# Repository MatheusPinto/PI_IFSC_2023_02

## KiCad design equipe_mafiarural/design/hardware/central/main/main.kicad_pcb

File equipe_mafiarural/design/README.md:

<!-- PROJECT LOGO -->
<div align="center">
  <h3 align="center">Sistema de Monitoramento de Vazamento de Gás de Cozinha</h3>

  <p align="center">
    <strong>(Design)</strong>
    <br />
</div>

## Índice

<!-- TABLE OF CONTENTS -->
<details>
  <summary>Table of Contents</summary>
  <ol>
    <li>
      <a href="#introdução">Introdução</a>
    </li>
    <li>
      <a href="#esquemático-de-funcionamento">Esquemático de Funcionamento</a>
      <ul>
        <li><a href="#módulo-central">Módulo Central</a></li>
        <li><a href="#módulo-de-sensoriamento">Módulo de Sensoriamento</a></li>
      </ul>
    </li>
    <li>
      <a href="#layout-da-placa-de-circuito-impresso">Layout da Placa de Circuito Impresso</a>
      <ul>
        <li><a href="#módulo-central-1">Módulo Central</a></li>
        <li><a href="#módulo-de-sensoriamento-1">Módulo de Sensoriamento</a></li>
      </ul>
    </li>
    <li>
      <a href="#modelo-3d-do-sistema">Modelo 3D do Sistema</a>
    </li>
    <li>
      <a href="#software">Software</a>
    </li>
  </ol>
</details>

---

## Introdução

Este documento detalha o design do projeto de um sistema de monitoramento de vazamento de gás de cozinha. O sistema será composto por um módulo central e dois módulos de sensoriamento.

## Esquemático de Funcionamento

O esquemático abaixo ilustra como funcionará a lógica do sistema. No caso deste projeto, serão utilizados apenas dois sensores que estarão conectados à central via rede, que por sua vez transmitirá os logs de monitoramento para o servidor ThingSpeak. 

<div style="display: flex; width: 100%; align-items: center; justify-content: space-around; gap: 20px;">

</div>
<br />

### Módulo Central

<br />

### Módulo de Sensoriamento

<br />

## Layout da Placa de Circuito Impresso

### Módulo Central

O módulo central terá entrada de 5 -12V e estará posicionada dentro do quadro de distribuição da residência. Para fazer o controle será utilizado um módulo de relés. Para o mantimento da alimentação após o corte de energia haverá uma célula Li-ion de 3.7V, sendo possível a expansão em paralelo para aumentar a capacidade de armazenamento.

<br />

### Módulo de Sensoriamento

O módulo de sensoriamento terá entrada de 5V via microUSB. Para o mantimento da alimentação após o corte de energia haverá uma célula Li-ion de 3.7V, sendo possível a expansão em paralelo para aumentar a capacidade de armazenamento.

<br />

## Modelo 3D do Sistema

Os sensores tem a principal qualidade de possibilitar a opção de o próprio usuário alocar sua posição. O recomendado é o mais próximo possível do chão e da potencial fonte de vazamento, considerando a densidade dos gases que desejamos detectar. No modelo abaixo, há dois sensores: Um posicionado logo ao lado da geladeira e outro acima da pia. A case ilustrada no modelo é apenas ilustrativa, não sendo a versão final do produto. A versão final da case estará disponível após testes com a placa e decisão final de componentes e periféricos.

<br />

## Software

A parte de monitoramento de logs e emissão de notificação será feita pelo servidor ThingSpeak. O código para o ESP32 será desenvolvido em C/C++ na IDE do Arduino. Como EXTRA, há a possibilidade de armazenar os comandos de controle em um cartão SD no módulo central, para que seja possível a atuação do sistema em caso de falha de conexão com a internet.

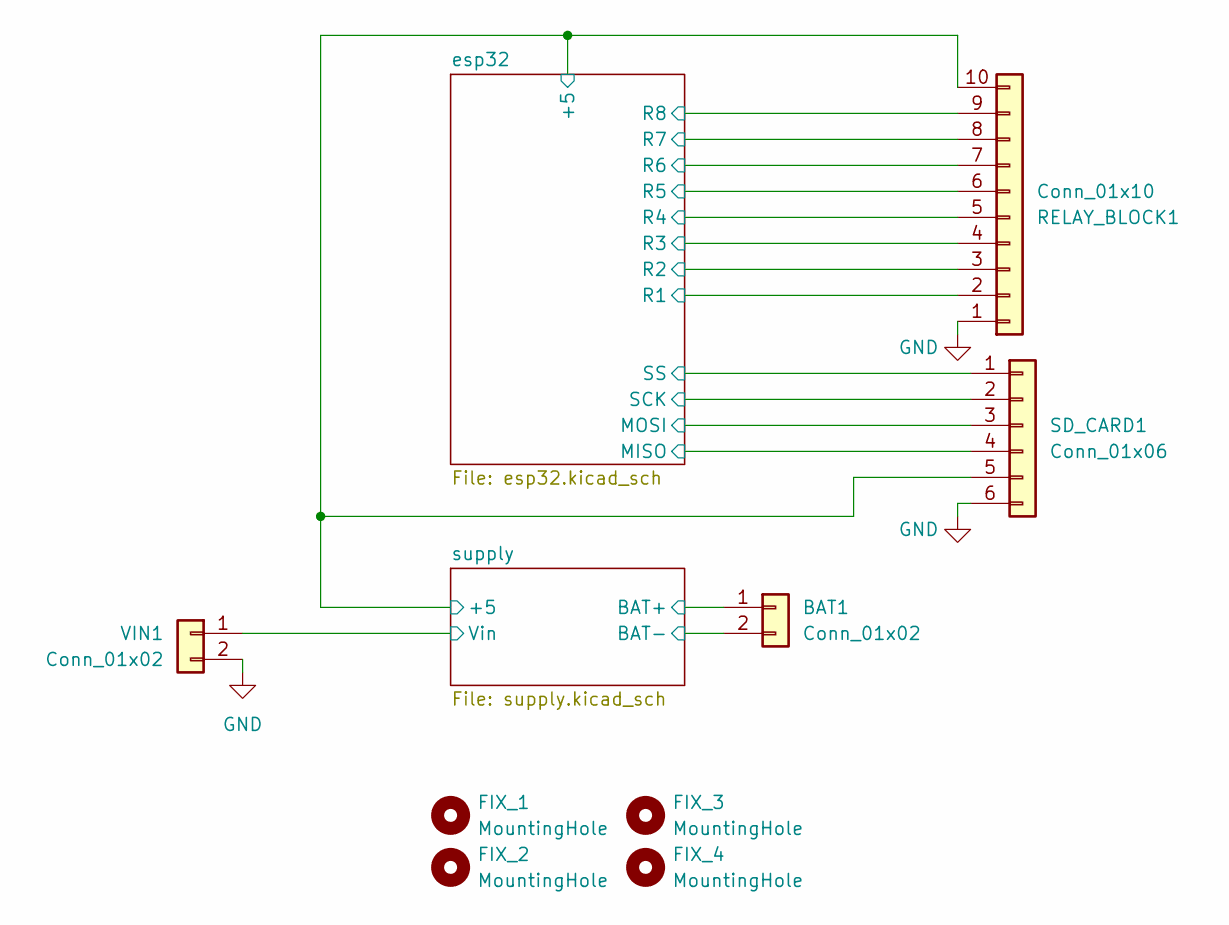
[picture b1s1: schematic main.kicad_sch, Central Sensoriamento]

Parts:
BAT1: Conn_01x02; PinHeader_1x02_P2.54mm_Vertical
FIX_1, FIX_2, FIX_3, FIX_4: MountingHole; MountingHole_3.5mm_Pad
RELAY_BLOCK1: Conn_01x10; PinSocket_1x10_P2.54mm_Vertical
SD_CARD1: Conn_01x06; PinSocket_1x06_P2.54mm_Vertical
VIN1: Conn_01x02; TerminalBlock_bornier-2_P5.08mm

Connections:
/esp32/+5: RELAY_BLOCK1.10, SD_CARD1.5; also elsewhere on the board
/esp32/MISO: SD_CARD1.4; also elsewhere on the board
/esp32/MOSI: SD_CARD1.3; also elsewhere on the board
/esp32/R1: RELAY_BLOCK1.2; also elsewhere on the board
/esp32/R2: RELAY_BLOCK1.3; also elsewhere on the board
/esp32/R3: RELAY_BLOCK1.4; also elsewhere on the board
/esp32/R4: RELAY_BLOCK1.5; also elsewhere on the board
/esp32/R5: RELAY_BLOCK1.6; also elsewhere on the board
/esp32/R6: RELAY_BLOCK1.7; also elsewhere on the board
/esp32/R7: RELAY_BLOCK1.8; also elsewhere on the board
/esp32/R8: RELAY_BLOCK1.9; also elsewhere on the board
/esp32/SCK: SD_CARD1.2; also elsewhere on the board
/esp32/SS: SD_CARD1.1; also elsewhere on the board
/supply/BAT+: BAT1.1; also elsewhere on the board
/supply/Vin: VIN1.1; also elsewhere on the board
GND: BAT1.2, RELAY_BLOCK1.1, SD_CARD1.6, VIN1.2; also elsewhere on the board

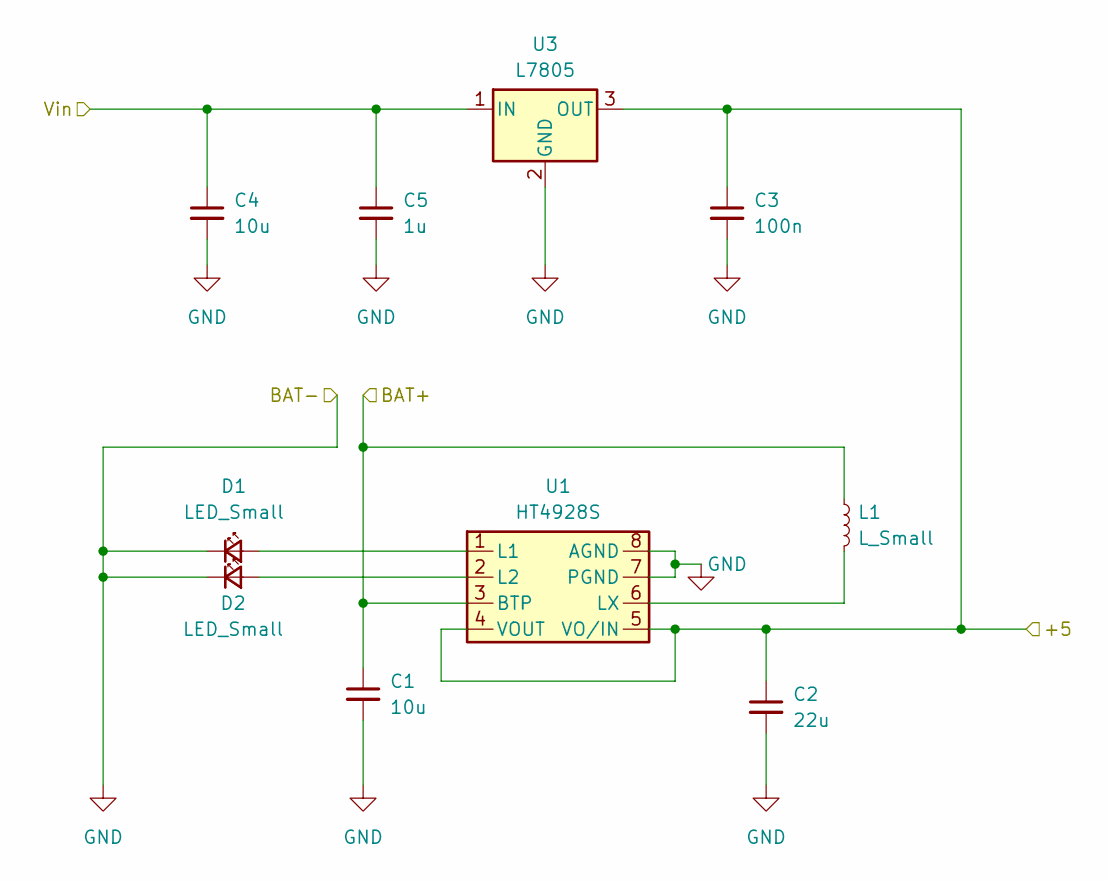
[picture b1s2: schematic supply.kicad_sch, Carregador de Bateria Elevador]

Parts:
C1: 10u; C_0805_2012Metric_Pad1.18x1.45mm_HandSolder
C2: 22u; C_1210_3225Metric_Pad1.33x2.70mm_HandSolder
C3: 100n; C_0805_2012Metric_Pad1.18x1.45mm_HandSolder
C4: 10u; CP_Radial_D5.0mm_P2.50mm
C5: 1u; CP_Radial_D5.0mm_P2.50mm
D1, D2: LED_Small; D_0805_2012Metric_Pad1.15x1.40mm_HandSolder
L1: L_Small; L_1812_4532Metric_Pad1.30x3.40mm_HandSolder
U1: HT4928S; SOP-8_3.9x4.9mm_P1.27mm
U3: L7805; TO-220-3_Vertical

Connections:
/esp32/+5: C2.1, C3.1, U1.4 (VOUT), U1.5 (VO/IN), U3.3 (OUT); also elsewhere on the board
/supply/BAT+: C1.1, L1.1, U1.3 (BTP); also elsewhere on the board
/supply/Vin: C4.1, C5.1, U3.1 (IN); also elsewhere on the board
GND: C1.2, C2.2, C3.2, C4.2, C5.2, D1.1 (K), D2.1 (K), U1.7 (PGND), U1.8 (AGND), U3.2 (GND); also elsewhere on the board
unnamed: D1.2 (A), U1.1 (L1)
unnamed: D2.2 (A), U1.2 (L2)
unnamed: L1.2, U1.6 (LX)

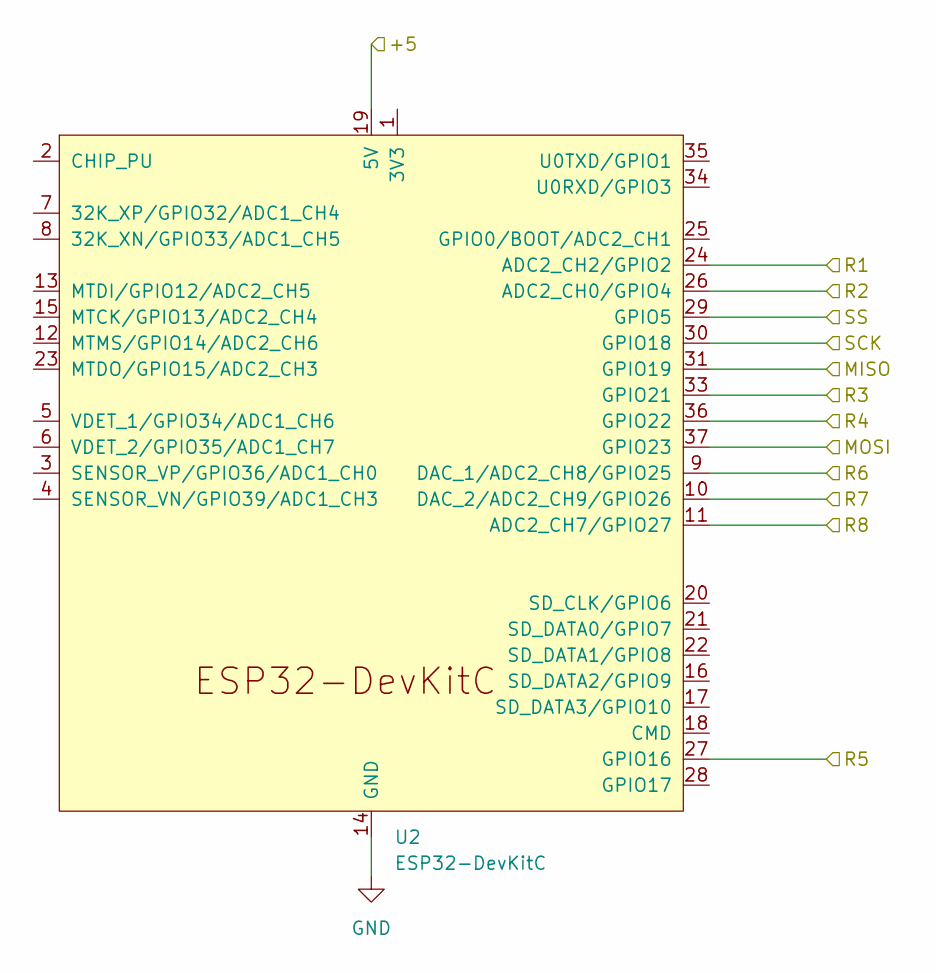
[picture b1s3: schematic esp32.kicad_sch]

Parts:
U2: ESP32-DevKitC

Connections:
/esp32/+5: U2.19 (5V); also elsewhere on the board
/esp32/MISO: U2.31 (GPIO19); also elsewhere on the board
/esp32/MOSI: U2.37 (GPIO23); also elsewhere on the board
/esp32/R1: U2.24 (ADC2_CH2/GPIO2); also elsewhere on the board
/esp32/R2: U2.26 (ADC2_CH0/GPIO4); also elsewhere on the board
/esp32/R3: U2.33 (GPIO21); also elsewhere on the board
/esp32/R4: U2.36 (GPIO22); also elsewhere on the board
/esp32/R5: U2.27 (GPIO16); also elsewhere on the board
/esp32/R6: U2.9 (DAC_1/ADC2_CH8/GPIO25); also elsewhere on the board
/esp32/R7: U2.10 (DAC_2/ADC2_CH9/GPIO26); also elsewhere on the board
/esp32/R8: U2.11 (ADC2_CH7/GPIO27); also elsewhere on the board
/esp32/SCK: U2.30 (GPIO18); also elsewhere on the board
/esp32/SS: U2.29 (GPIO5); also elsewhere on the board
GND: U2.14 (GND), U2.32 (GND), U2.38 (GND); also elsewhere on the board

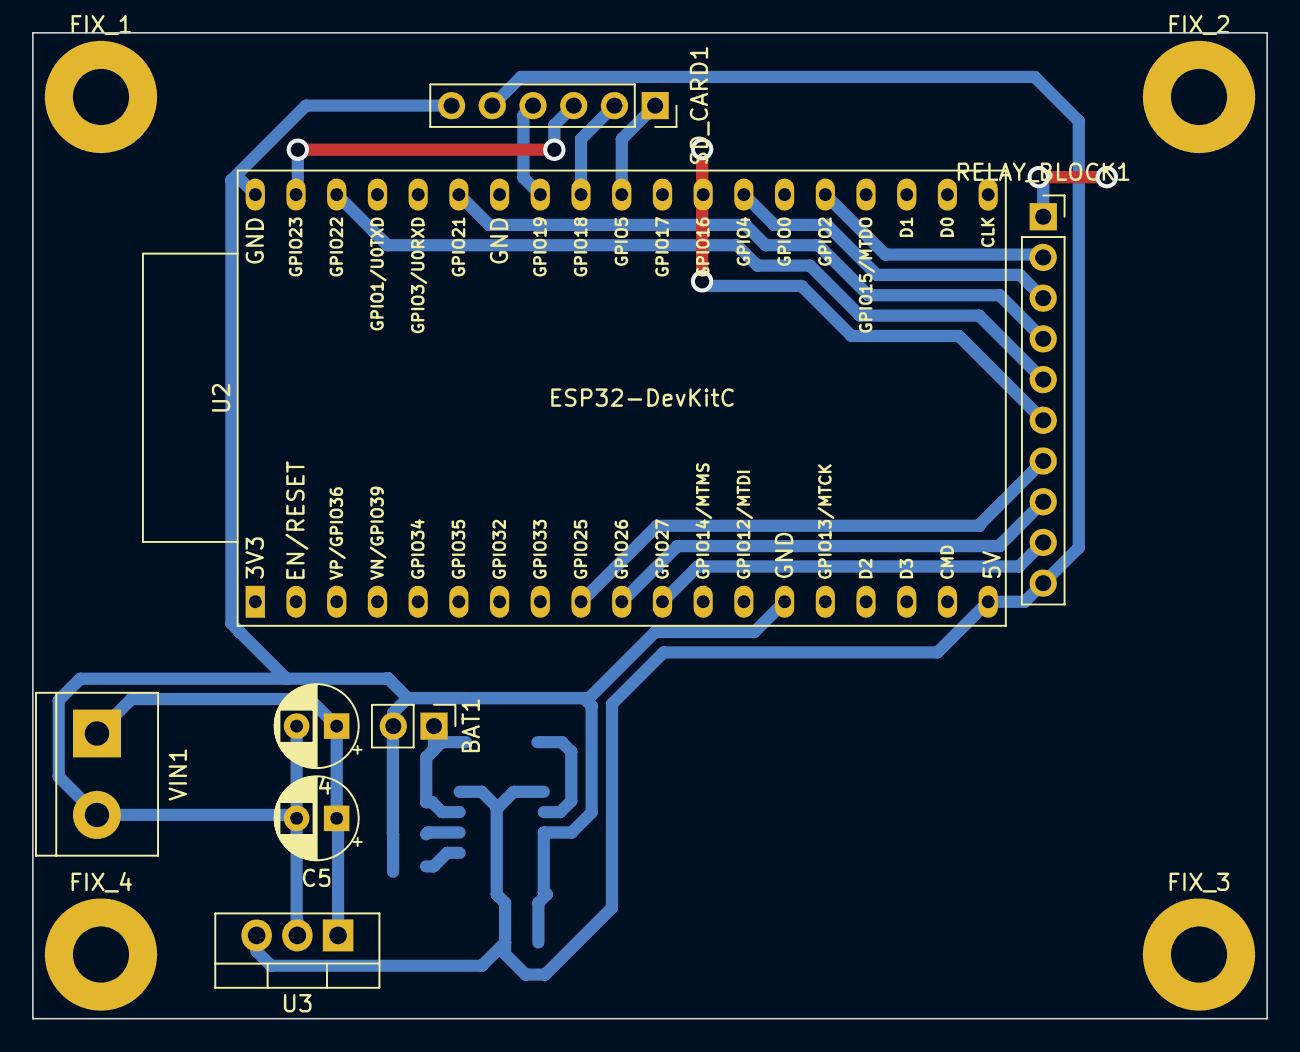
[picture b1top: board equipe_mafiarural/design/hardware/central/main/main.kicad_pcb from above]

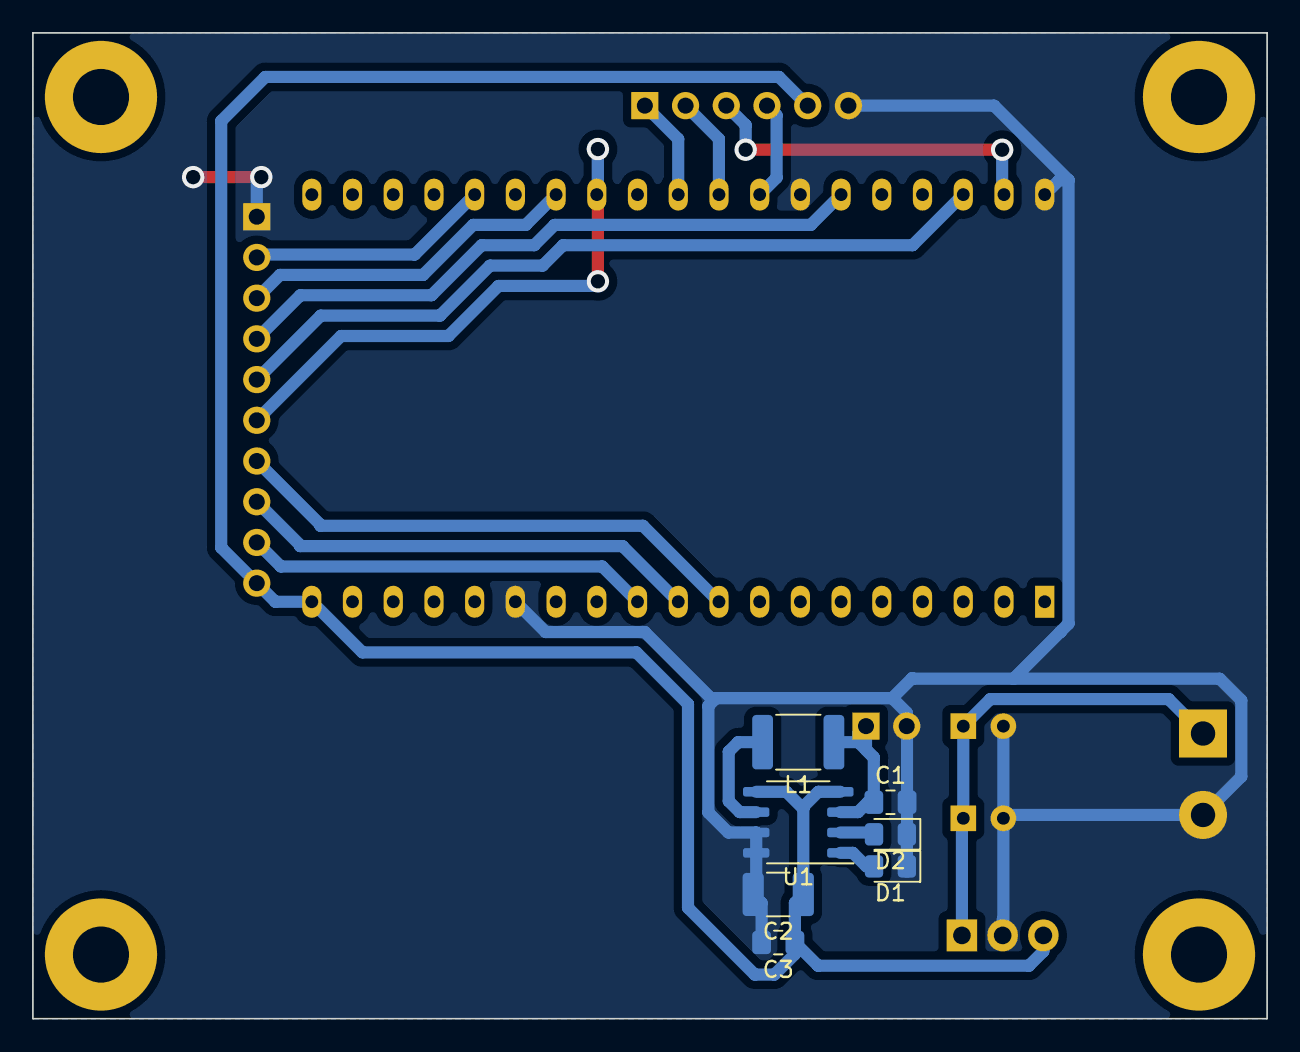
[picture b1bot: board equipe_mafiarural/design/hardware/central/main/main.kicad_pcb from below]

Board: 2 copper layers, 77.0 x 61.5 mm, 19 parts (7 on the bottom side), 19 nets.

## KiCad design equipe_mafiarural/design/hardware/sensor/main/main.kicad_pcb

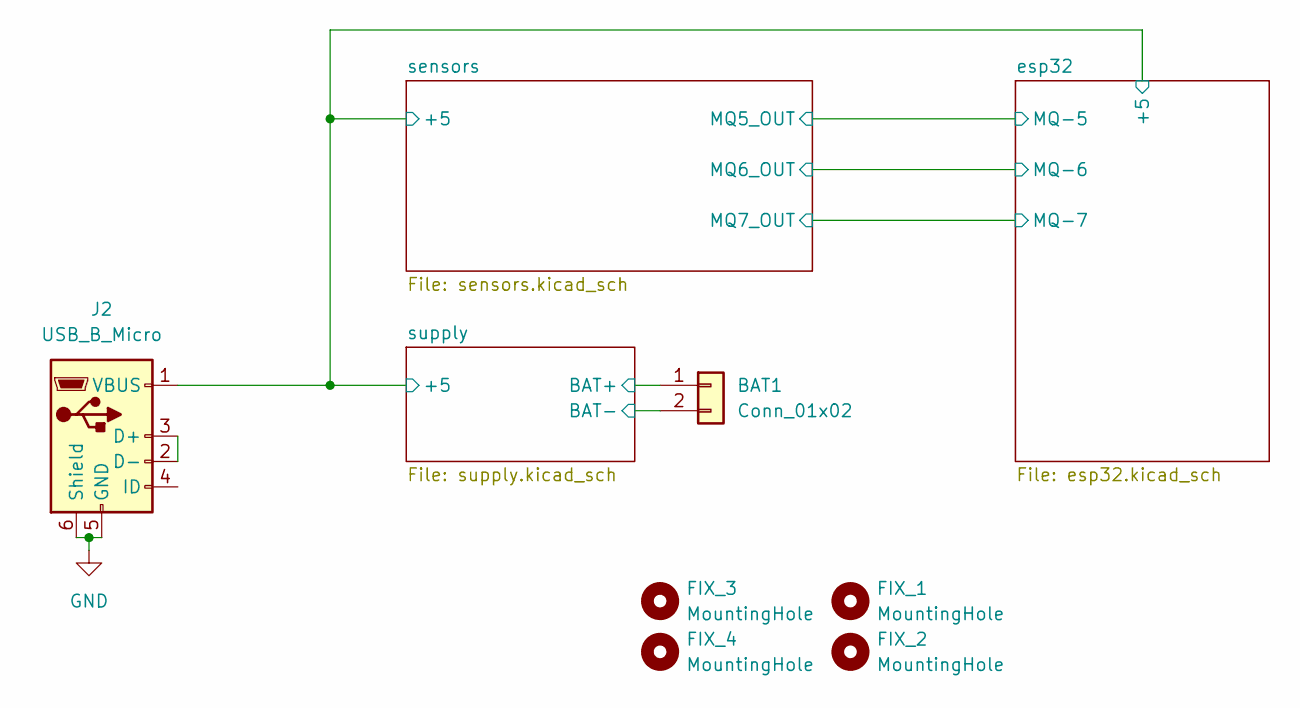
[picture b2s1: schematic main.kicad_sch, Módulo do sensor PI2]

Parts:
BAT1: Conn_01x02; PinHeader_1x02_P2.54mm_Vertical
FIX_1, FIX_2, FIX_3, FIX_4: MountingHole; MountingHole_3.5mm_Pad
J2: USB_B_Micro; USB_Micro-B_Amphenol_10118193-0002LF_Horizontal

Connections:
/esp32/+5: J2.1 (VBUS); also elsewhere on the board
/supply/BAT+: BAT1.1; also elsewhere on the board
GND: BAT1.2, J2.5 (GND), J2.6 (Shield); also elsewhere on the board

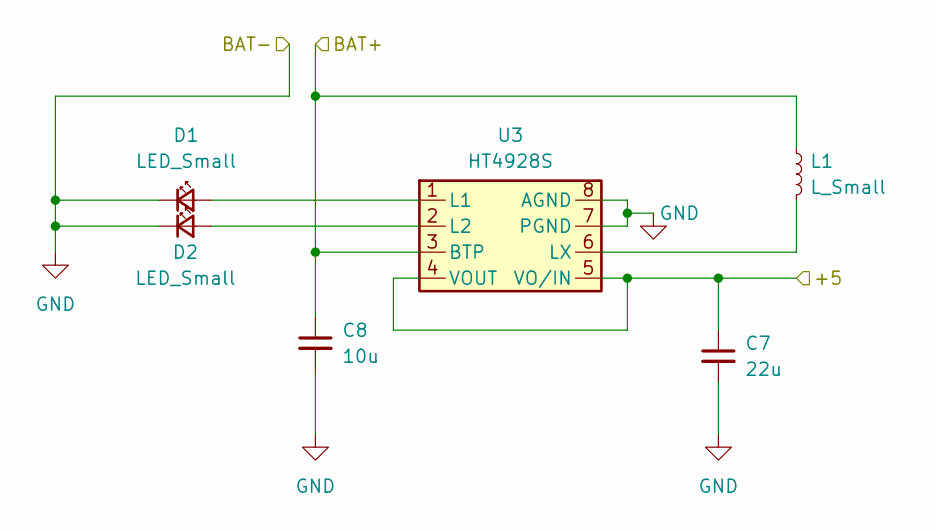
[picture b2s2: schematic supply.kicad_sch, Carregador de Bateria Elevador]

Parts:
C7: 22u; C_1210_3225Metric_Pad1.33x2.70mm_HandSolder
C8: 10u; C_0805_2012Metric_Pad1.18x1.45mm_HandSolder
D1, D2: LED_Small; D_0805_2012Metric_Pad1.15x1.40mm_HandSolder
L1: L_Small; L_1812_4532Metric_Pad1.30x3.40mm_HandSolder
U3: HT4928S; SOP-8_3.9x4.9mm_P1.27mm

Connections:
/esp32/+5: C7.1, U3.4 (VOUT), U3.5 (VO/IN); also elsewhere on the board
/supply/BAT+: C8.1, L1.1, U3.3 (BTP); also elsewhere on the board
GND: C7.2, C8.2, D1.1 (K), D2.1 (K), U3.7 (PGND), U3.8 (AGND); also elsewhere on the board
unnamed: D1.2 (A), U3.1 (L1)
unnamed: D2.2 (A), U3.2 (L2)
unnamed: L1.2, U3.6 (LX)

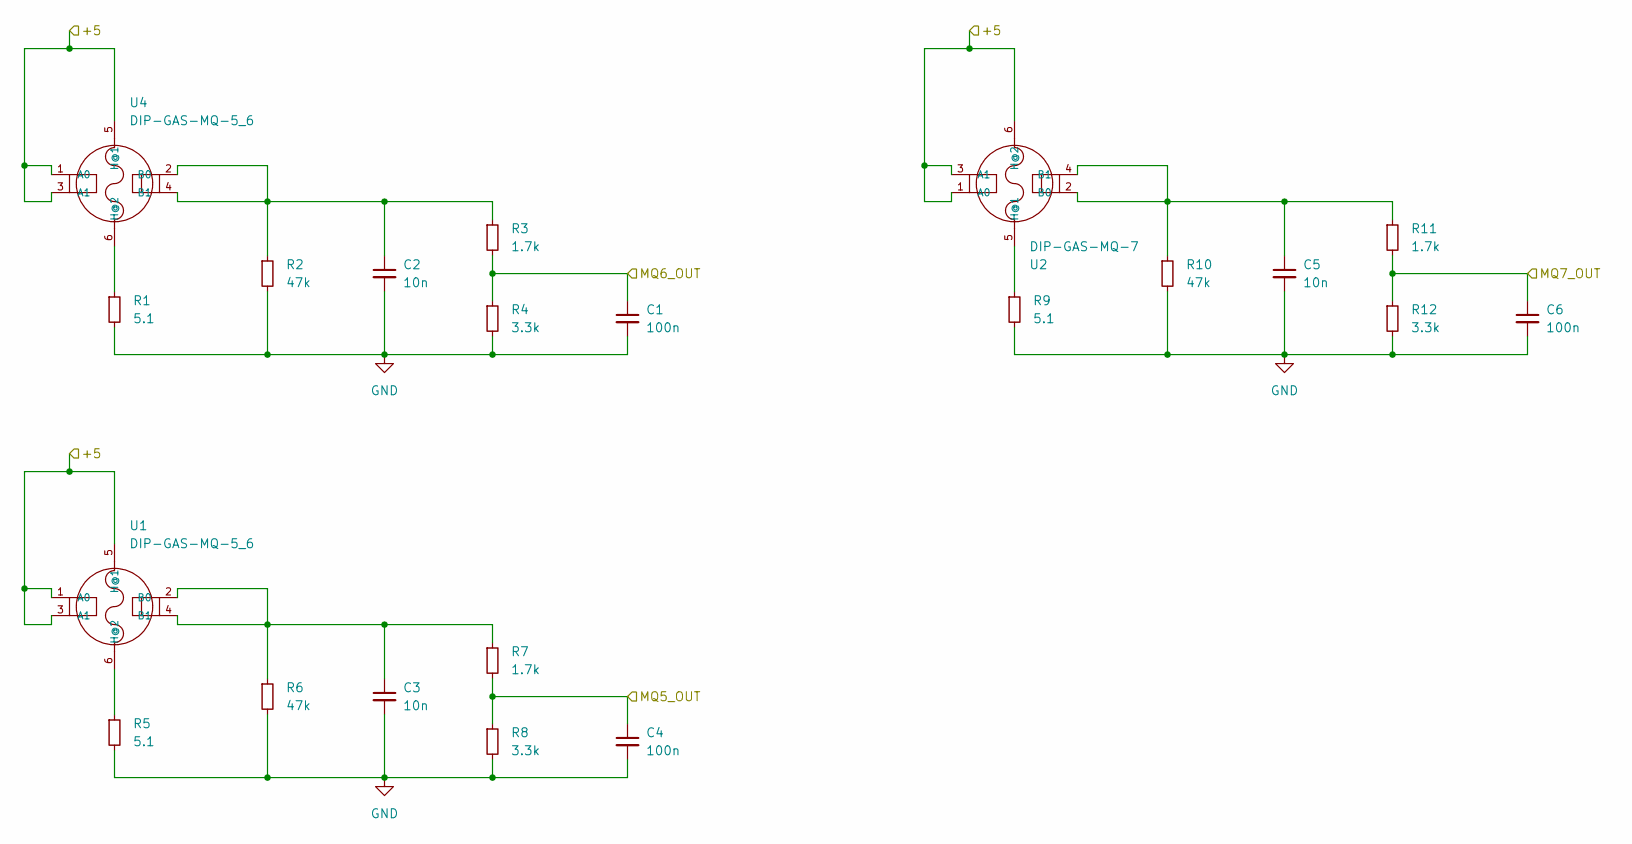
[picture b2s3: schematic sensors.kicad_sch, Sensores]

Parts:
C1, C4, C6: 100n; C_0805_2012Metric_Pad1.18x1.45mm_HandSolder
C2, C3, C5: 10n; C_0805_2012Metric_Pad1.18x1.45mm_HandSolder
R1, R5, R9: 5.1; R_0805_2012Metric_Pad1.20x1.40mm_HandSolder
R2, R6, R10: 47k; R_0805_2012Metric_Pad1.20x1.40mm_HandSolder
R3, R7, R11: 1.7k; R_0805_2012Metric_Pad1.20x1.40mm_HandSolder
R4, R8, R12: 3.3k; R_0805_2012Metric_Pad1.20x1.40mm_HandSolder
U1, U4: DIP-GAS-MQ-5_6; SNR6; MPN MQ-5
U2: DIP-GAS-MQ-7; MQ-7; MPN MQ-5

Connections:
/esp32/+5: U1.1 (A0), U1.3 (A1), U1.5 (H@1), U2.1 (A0), U2.3 (A1), U2.6 (H@2), U4.1 (A0), U4.3 (A1), U4.5 (H@1); also elsewhere on the board
/esp32/MQ-5: C4.1, R7.2, R8.1; also elsewhere on the board
/esp32/MQ-6: C1.1, R3.2, R4.1; also elsewhere on the board
/esp32/MQ-7: C6.1, R11.2, R12.1; also elsewhere on the board
GND: C1.2, C2.2, C3.2, C4.2, C5.2, C6.2, R1.2, R2.2, R4.2, R5.2, R6.2, R8.2, R9.2, R10.2, R12.2; also elsewhere on the board
unnamed: C3.1, R6.1, R7.1, U1.2 (B0), U1.4 (B1)
unnamed: R5.1, U1.6 (H@2)
unnamed: C5.1, R10.1, R11.1, U2.2 (B0), U2.4 (B1)
unnamed: R9.1, U2.5 (H@1)
unnamed: C2.1, R2.1, R3.1, U4.2 (B0), U4.4 (B1)
unnamed: R1.1, U4.6 (H@2)

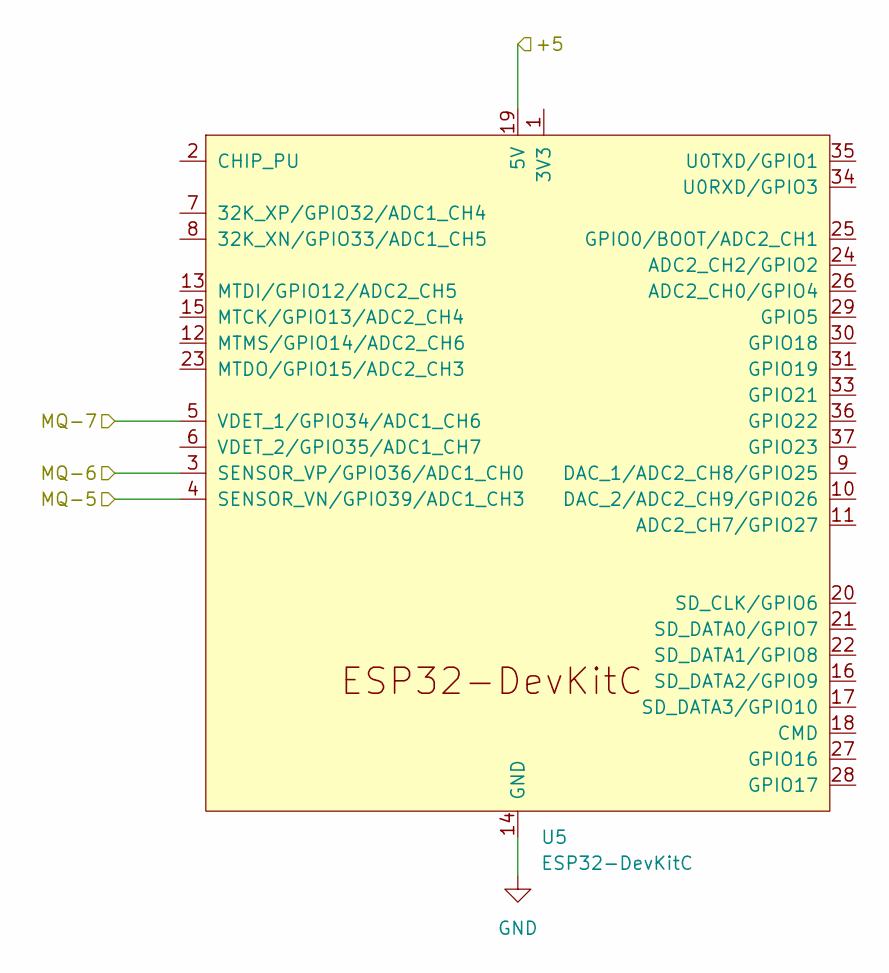
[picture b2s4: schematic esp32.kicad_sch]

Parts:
U5: ESP32-DevKitC

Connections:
/esp32/+5: U5.19 (5V); also elsewhere on the board
/esp32/MQ-5: U5.4 (SENSOR_VN/GPIO39/ADC1_CH3); also elsewhere on the board
/esp32/MQ-6: U5.3 (SENSOR_VP/GPIO36/ADC1_CH0); also elsewhere on the board
/esp32/MQ-7: U5.5 (VDET_1/GPIO34/ADC1_CH6); also elsewhere on the board
GND: U5.14 (GND), U5.32 (GND), U5.38 (GND); also elsewhere on the board

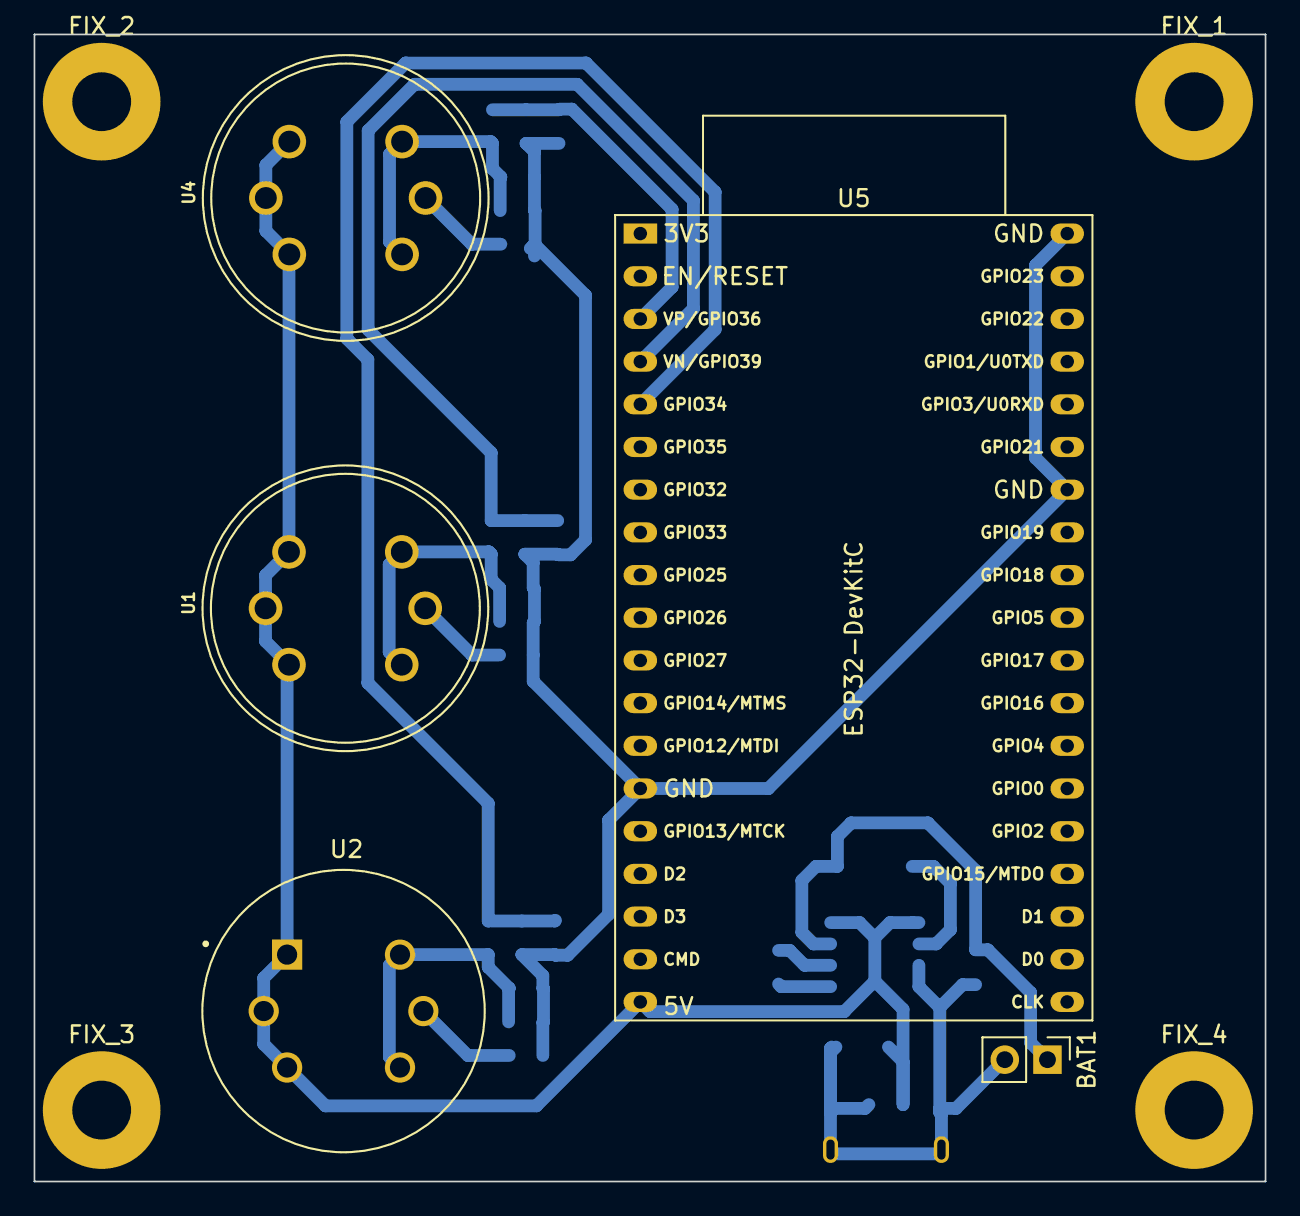
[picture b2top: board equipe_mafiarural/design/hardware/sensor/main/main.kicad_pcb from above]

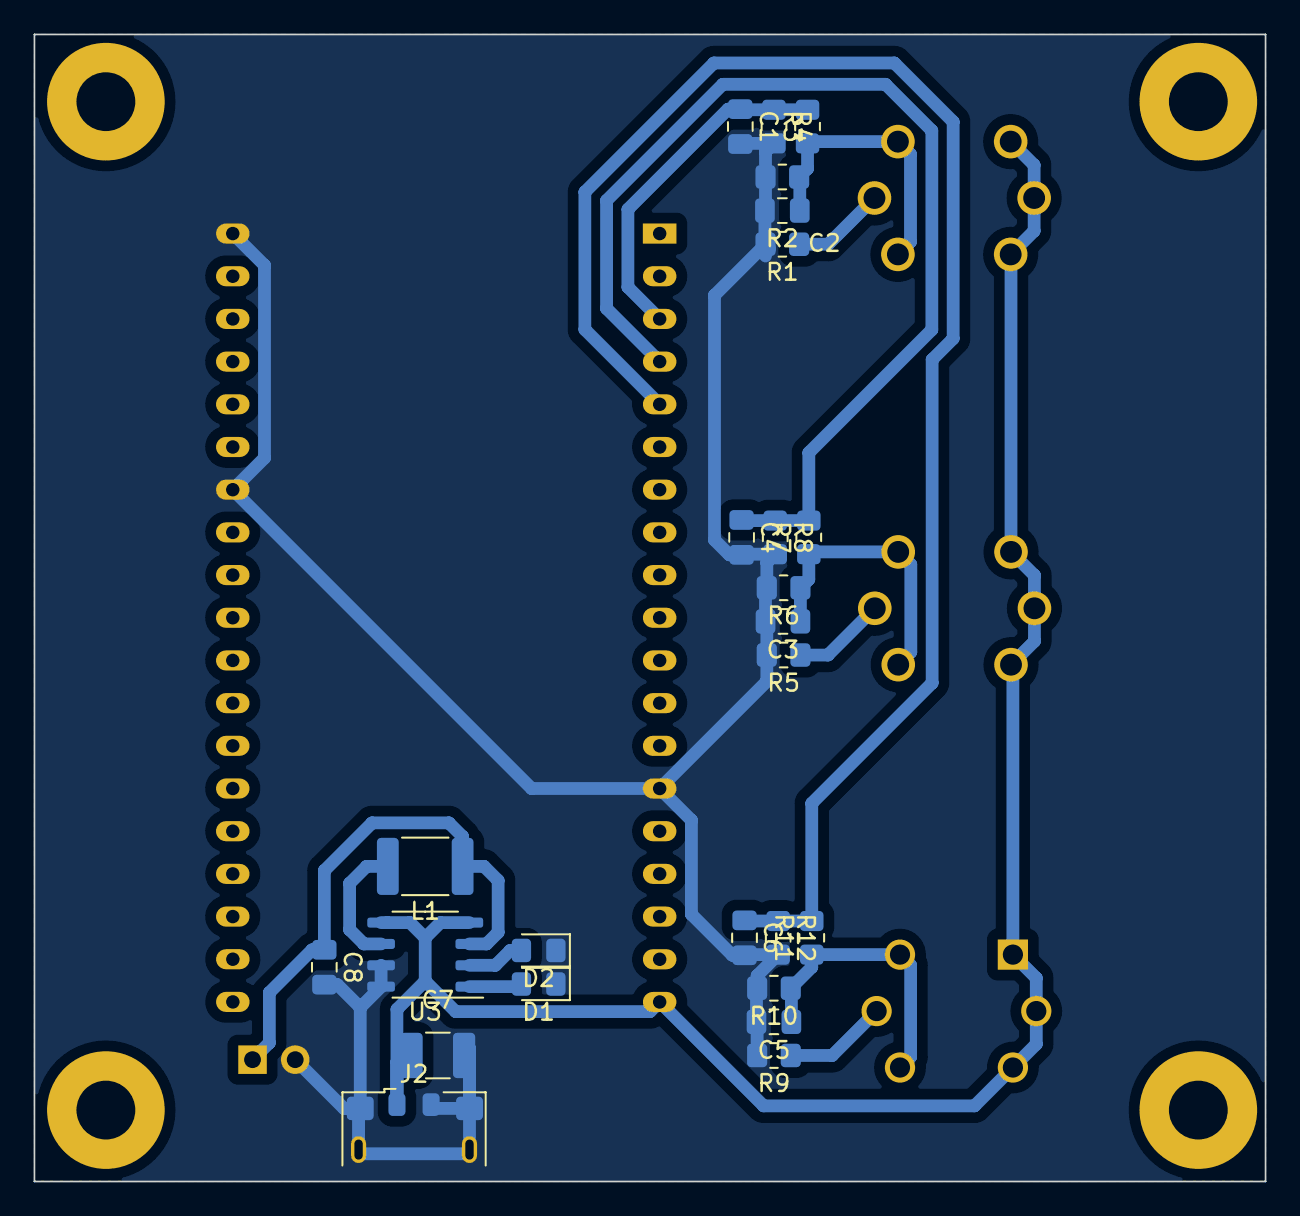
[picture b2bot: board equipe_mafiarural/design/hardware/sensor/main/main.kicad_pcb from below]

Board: 2 copper layers, 73.2 x 68.2 mm, 34 parts (25 on the bottom side), 15 nets.

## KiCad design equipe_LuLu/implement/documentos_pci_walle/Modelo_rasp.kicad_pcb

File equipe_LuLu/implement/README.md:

# Implementação do projeto

A implementação do projeto está dividia em duas partes principais: código e montagem.

## Código do projeto

Os códigos principais do projeto estão no diretório ['codigo/'](codigo/). São códigos referentes a interface e comunicação do cliente com o Wall-e.

A documentação dos módulos e submódulos em Python criados para implementar o Wall-e está disponível na página de [documentação dos módulos](docs/_build/markdown/index.md) e foi criada usando o [Sphinx](https://www.sphinx-doc.org/en/master/). Para gerá-la, consulte a pasta [docs/](docs/).

A configuração da Raspberry Pi para o projeto está disponível na seguinte página: [configuração da Raspberry Pi](codigo/raspberry/).

Além disso, a documentação referente ao [treinamento da indentifiação de lixo](codigo/identificador) e ao [treinamento do algorítimo de segmentação](codigo/segmentacao) também estão no diretório do [código](codigo).

## Montagem

A documentação dos testes e validação do circuito inicial está disponível na página [teste e validação do circuito elétrico](validacoes_circuito_eletrico.md). A documentação dos testes finais como o wall-e montado está na página [testes finais](testes_finais.md).

Os arquivos da PCI estão disponíveis na pasta de [documentos da PCI](documentos_pci).

# Resultados

O Wall-e está andando por conta própria e identificando lixo (caixa de leite), como mostrado no [vídeo de teste de colisão e identificação do lixo](https://www.youtube.com/watch?v=cx0_UOhC5lk). Mais informações sobre os resultados estão disponíveis na página de [resultados](Resultados.md).

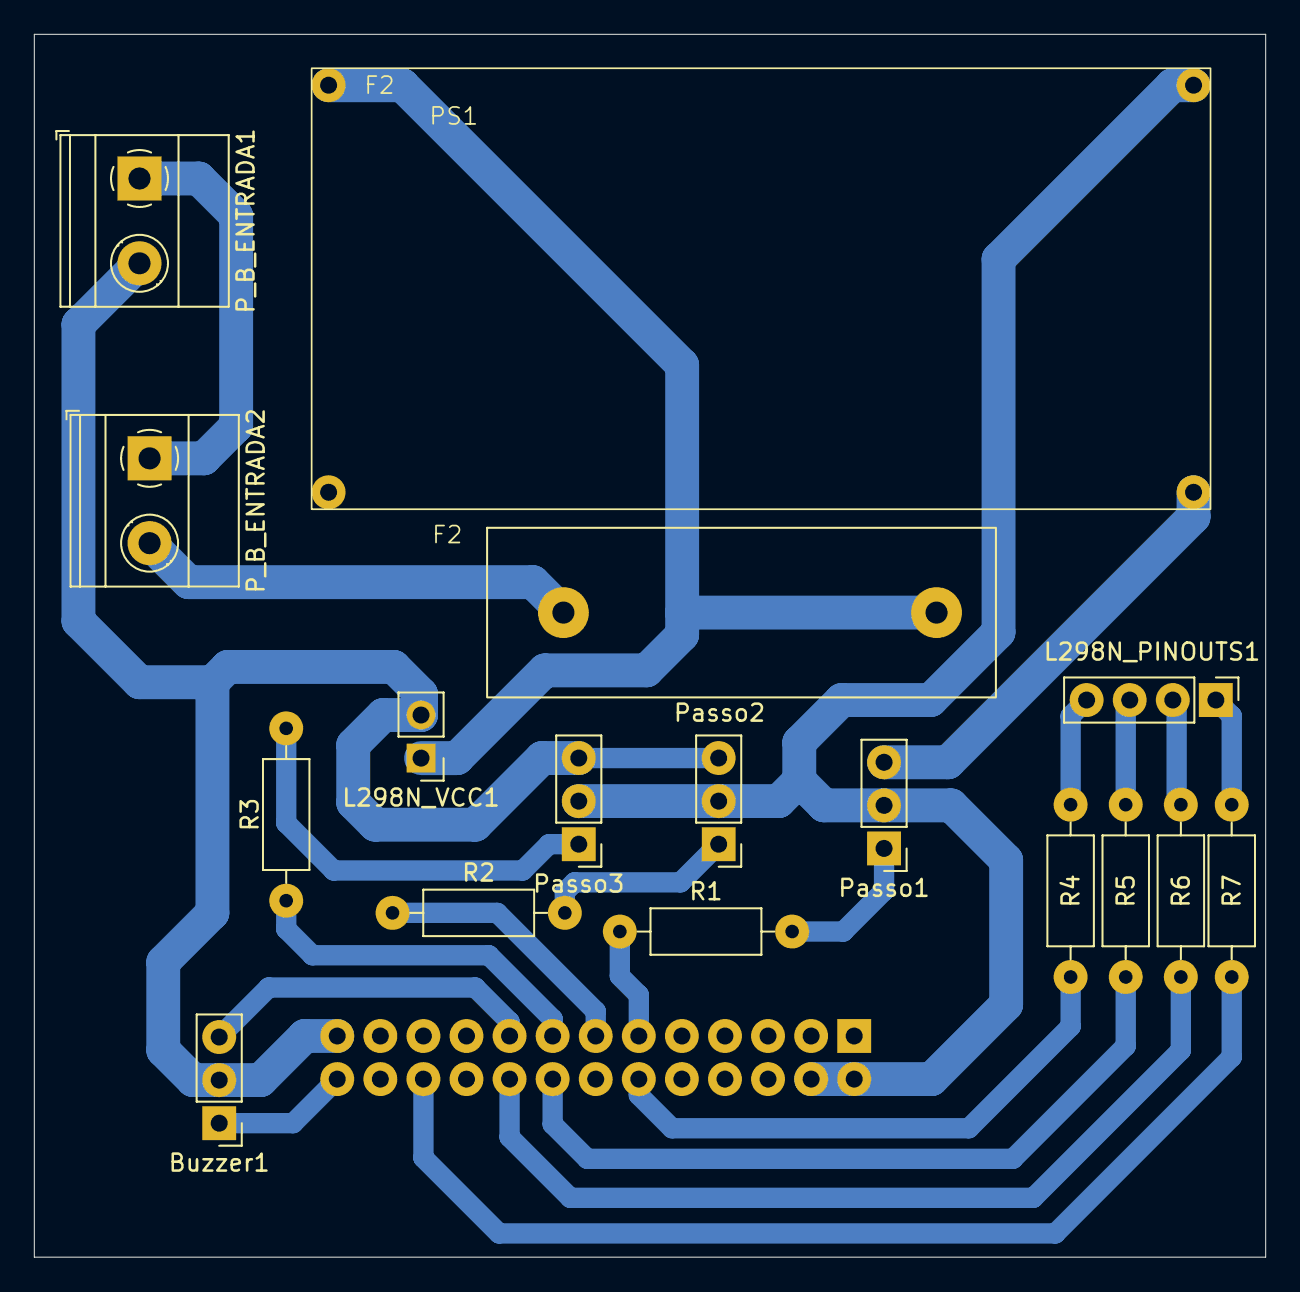
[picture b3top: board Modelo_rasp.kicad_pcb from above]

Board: 2 copper layers, 72.6 x 72.1 mm, 18 parts (1 on the bottom side), 21 nets.

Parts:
Buzzer1: Screw_Terminal_01x03; PinHeader_1x03_P2.54mm_Vertical
F2: Fuse; Fusivel
J1: GPIO; PinSocket_2x13_P2.54mm_Vertical
L298N_PINOUTS1: L298N_PINOUTS; PinHeader_1x04_P2.54mm_Vertical
L298N_VCC1: Screw_Terminal_01x02; PinHeader_1x02_P2.54mm_Vertical
PS1: Buck_step_down; Buck
P_B_ENTRADA1, P_B_ENTRADA2: Screw_Terminal_01x02; TerminalBlock_Phoenix_MKDS-1,5-2_1x02_P5.00mm_Horizontal
Passo1, Passo2, Passo3: Screw_Terminal_01x03; PinHeader_1x03_P2.54mm_Vertical
R1, R2, R3, R4, R5, R6, R7: R; R_Axial_DIN0207_L6.3mm_D2.5mm_P10.16mm_Horizontal

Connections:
+3V3: Buzzer1.3, J1.1, J1.17
+5V: J1.2, J1.4, PS1.4 (+Vout), Passo1.2, Passo2.2, Passo3.2
/GPIO7/SPI0.CE1: Buzzer1.1, J1.26
/GPIO17: J1.11, R1.1
/GPIO18/PCM.CLK: J1.12, R4.1
/GPIO22: J1.15, R3.1
/GPIO23: J1.16, R5.1
/GPIO24: J1.18, R6.1
/GPIO25: J1.22, R7.1
/GPIO27: J1.13, R2.1
GND: Buzzer1.2, J1.6, J1.9, J1.14, J1.20, J1.25, L298N_VCC1.2, PS1.1 (-Vin), PS1.3 (-Vout), P_B_ENTRADA1.2, Passo1.3, Passo2.3, Passo3.3
unnamed: L298N_PINOUTS1.1, R7.2
unnamed: L298N_PINOUTS1.2, R6.2
unnamed: L298N_PINOUTS1.3, R5.2
unnamed: L298N_PINOUTS1.4, R4.2
unnamed: F2.2, L298N_VCC1.1, PS1.2 (+Vin)
unnamed: P_B_ENTRADA1.1, P_B_ENTRADA2.1
unnamed: F2.1, P_B_ENTRADA2.2
unnamed: Passo1.1, R1.2
unnamed: Passo2.1, R2.2
unnamed: Passo3.1, R3.2

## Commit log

2023-10-17 commit design
2023-10-28 Added base of implement code
2023-11-02 arquivo md alterado para README
2023-11-28 Feat: código da interface
2023-11-28 Test: scripts de teste da interface
2023-11-28 Feat: código co controlador
2023-11-28 Test: scripts de teste do controlador
2023-11-29 Doc: documentação da Raspberry Pi
    Também adiciona um script para configurar o Dropbear e o binário do
    Tensorflow runtime compilado para a Raspberry Pi.
2023-11-29 Feat: gerar datasets para segmentação
    Usa computação gráfica para gerar as imagens do dataset
2023-11-29 Feat: código da segmentação
    Disponibiliza um modelo de segmentação focado nos corredores verdes do IFSC.
2023-11-29 Test: scripts de teste da segmentação
2023-11-29 Doc: documentação do código em Python com Sphinx
    Apenas foi adicionado o código da interface, controlador e segmentador.
2023-11-29 Doc: Implementação do Haar_Cascade, Kicad, Testes finais, Validações.
2023-11-30 Docs - Imagens Implement
2023-11-30 Docs: Implement - haar_cascade, Kicad.
2023-11-30 Docs: Implement - Correção haar_cascade
2023-11-30 Docs: Implement, Modulo dos motores
2023-11-30 Docs: Implemente - Correções
2023-11-30 Docs: Implement - Atualização Testes_finais
2023-11-30 Implement Equipe Mafia Rural
2023-11-30 IMPLEMENT ESTUFA HIDROPÔNICA VERTICAL INTELIGENTE
2023-11-30 software e readme
2023-11-30 Feat: documentação e teste da movimentação
2023-11-30 Feat: classe para detecção de lixo
2023-11-30 Dc: Ajuste de documentação
    Ajusta a documentação do segmentador, controlador e interface.
2023-11-30 Feat: configurações de ambiente
2023-11-30 Feat: código principal e teste
    Ainda não está plenamente funcional.
2023-11-30 Doc: documentação geral do implement
2023-11-30 Doc: atualiza a documentação do Sphinx
    Adicioona os demais módulos que estavam faltando.
2023-11-30 Fix: adiciona o modelo Haar cascade.
    Esse modelo não foi adicionado junto ao código do identificador.
2023-11-30 Doc: corrige erros na documentacao
2023-12-07 Feat: modo autônomo funcionando
    Foi necessário refatorar os seguintes submódulos:
    - controlador
    - segmentacao
    E ajustar os seguintes módulos:
    - identificacao
    - movimentacao
2023-12-07 Doc: atualiza documentação do Sphinx
    Novo template para os módulos. Adiciona a pasta e arquivo de origem do
    código.
2023-12-07 Implement - Atualização e correção
2023-12-08 Implement - Correção e adição do novo modelo de identificação
2023-12-08 Implement - Adição do resultado final
2023-12-13 Feat: melhora o controlador e segmentador
    Controlador não considera a região do objeto identificado como região
    colidível.
    Segmentador também pode funcionar com modelos com 2 canais na saída.
2023-12-18 adicionando video de testes da estufa
2023-12-19 Added code implementation and code README
    Added code implementation for the modules:
    * Sensor
    * Central
    Added compatibility with painlessMesh for inte node communication and
    added MQTT broker support in central node for Computer Network grade
    final work.
2023-12-19 Feat: criação do novo modelo
    Adiciona o código para criar o modelo que foi apresentado dia 13/12/2023
    na SMM1, e sua documentação.
2023-12-19 Docs: instruções de uso. Renomeia a classe 'Passo'
    Adiciona instruções de uso do código final (com a Raspberry Pi já
    configurada). Isso facilita caso o leitor apenas deseje usar o projeto
    já feito, como na SNCT.
    Antes a classe que controla um servo motor se chamava 'Passo'. Foi
    renomeada para o nome correto: 'Servo'.
2023-12-19 Doc: erro gramatical. IP de loopback no exemplo.
    O IP de loopback é adicionado como um exemplo ao arquivo
    'equipe_LuLu/implement/codigo/env.exemplo/conf'. Ele não é usado por
    padrão. Se o usuário deseja, deve selecioná-lo por conta própria.
